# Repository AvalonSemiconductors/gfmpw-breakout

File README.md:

# gfmpw-breakout
This repo contains all the files, including production-ready gerber files, for this PCB:

It contains all components on-board to keep the caravel management controller happy and breaks out the user IO lines into the same footprint as a DIP-40 IC. The board is meant for both prototyping, i.e. on a breadboard, or use as a module on another PCB.

Specifically, it has:

 - Space for any GFMPW IC
 - Spiflash IC for mangement controller firmware, plus required level shifters and 3.3V voltage regulator
 - Programming header for SPI flash
 - Power-on reset circuitry
 - LED on ``gpio``
 - Breakouts for pins ``mprj_io[37:5]`` as well as ``mprj_io[0]``, ``mprj_io[1]`` and ``mprj_io[4]``

Note: the board does not have the capability to program the 25Q32 spiflash in-place. To program it, any number of portable ROM programmers can be used, such as the [CH341A](https://www.amazon.com/Programmer-Module-CH341A-Burner-5V-3-3V/dp/B07PFCJ8G9) (I recommend this device as it is supported by the `flashrom` utility on most Linux distros) and wire the programming header to it.

The pinout of the board is as such (a KiCad symbol is [also available](board_symbol.kicad_sym)):

Note that 3V3 is a output from the on-board voltage regulator. The only power input is 5V.

To edit the KiCad files, you will need to add the ``Caravel_Board.pretty`` footprint files from the efabless/caravel_board repo, which can be obtained [here](https://github.com/efabless/caravel_board/tree/main/hardware/footprints/Caravel_Board.pretty).

# BOM

| Designator(s) | Value       | TME # | Mouser # |
|---------------|-------------|-------|----------|
| U1         | AMS1117-3.3 | AZ1117H-3.3TRE1 | 595-REG1117-3.3 |
| U2         | 25Q32 or compatible       | MX25L1006EMI-10G | 454-W25Q32JVSSIMTR |
| U3         | MCP1319MT | MCP1319MT-29LT | 579-MCP1319MT29LE/OT |
| U4         | GFMPW IC | N/A | N/A |
| U5, U6, U7, U8 | SN74LV1T126 | - |  595-74LV1T126QDBVRQ1 |
| D1, D2 | LED 1206 (metric 3216) | 24-21SURC/S530-A2 | 630-HSMH-H150 |
| R4, R5, R6 | 1K 1206 (metric 3216) | 1206S4F1001T5E | 71-RCA12061K00JNEA |
| C1, C2, C3 | 1µF 0805 (metric 2012) | 08053C105J4T2A | 810-CGA4J3X7R1H105MS |

Assembled board should look like this:

After building, the programmer hookup (CH341A) is like follows. This may even work for in-system programming, but the programmer powers the board, so its intended to be a standalone setup.
Note that connecting the programmer holds caravel in reset until the physical connections to the programmer are disconnected.

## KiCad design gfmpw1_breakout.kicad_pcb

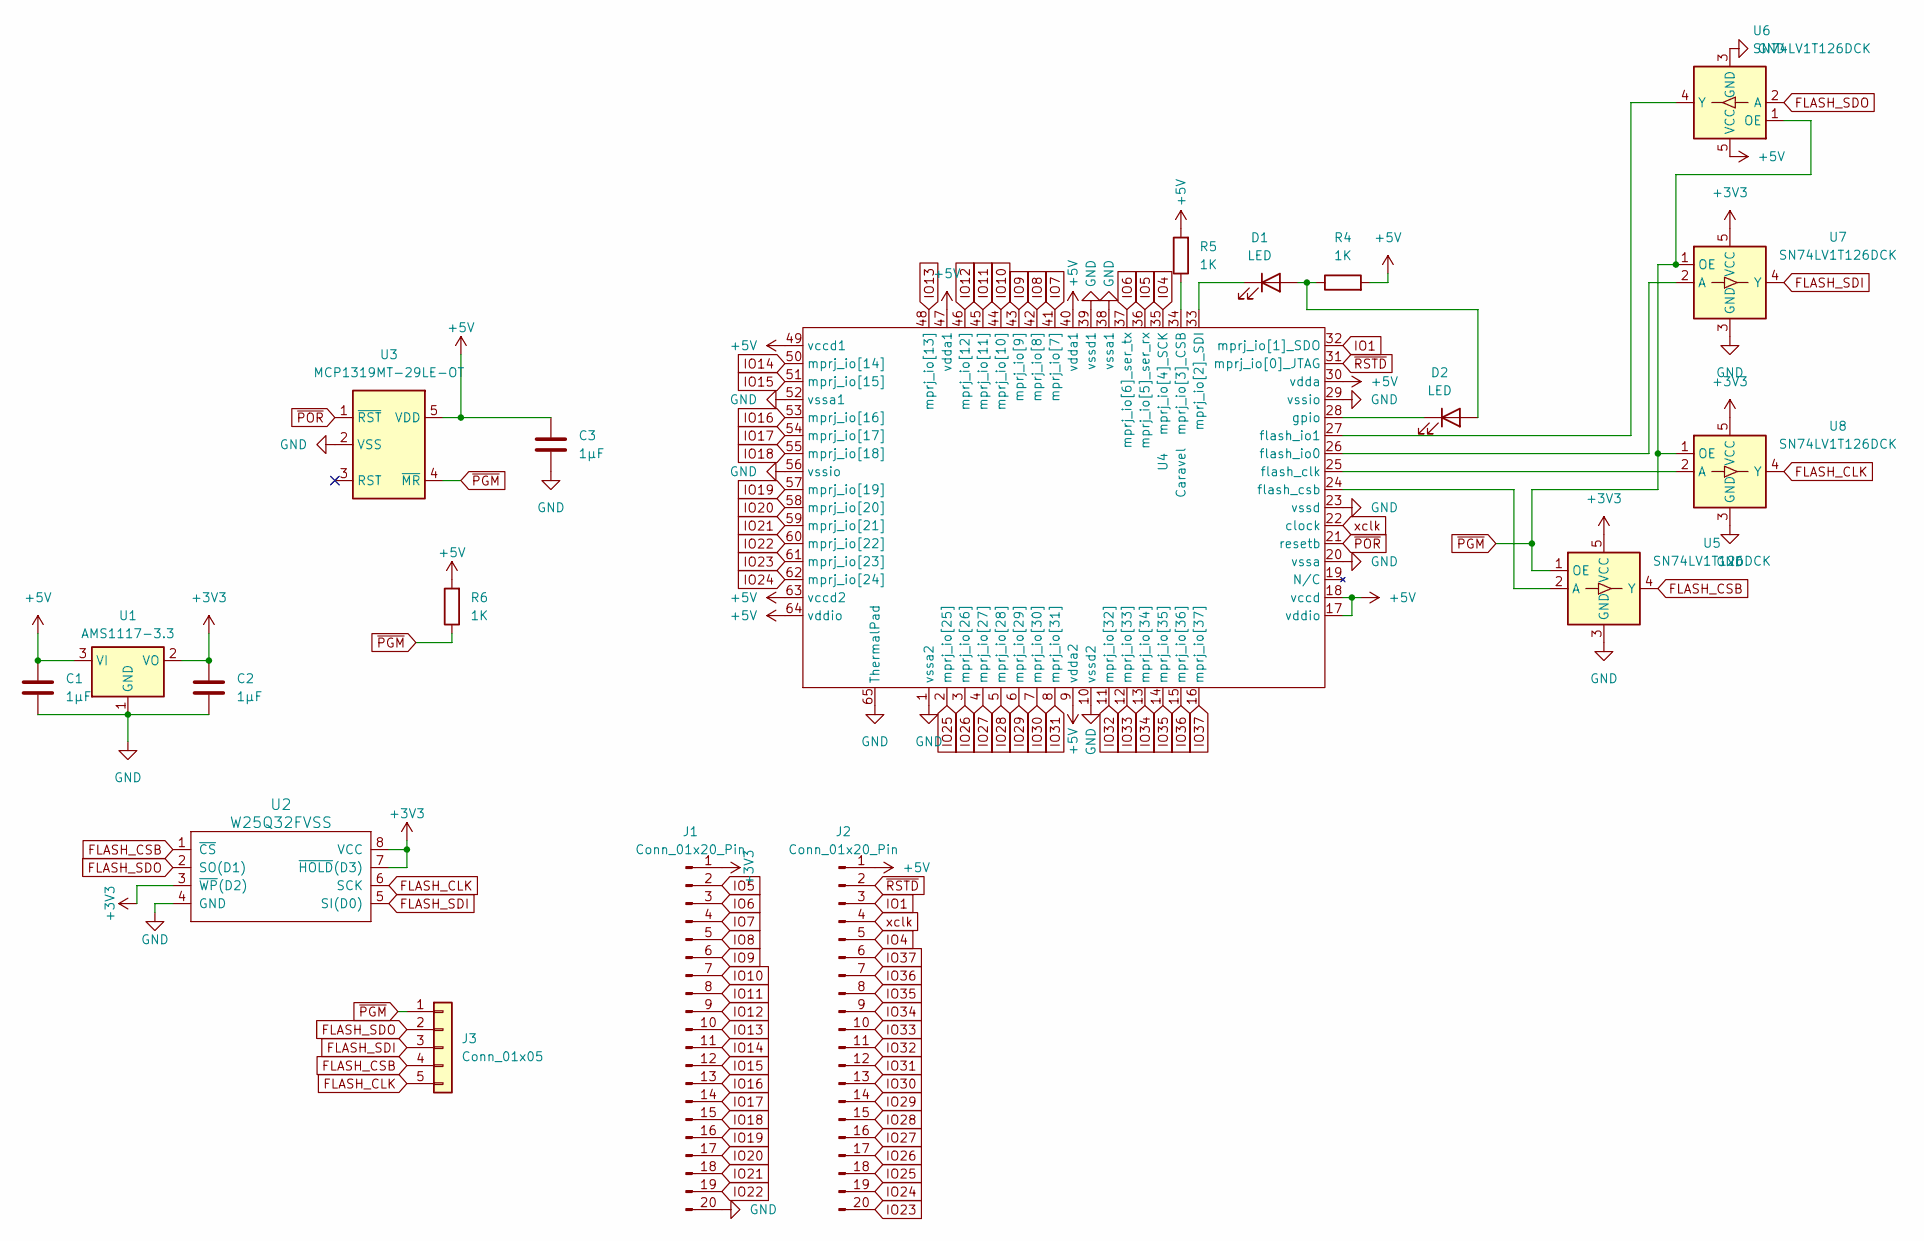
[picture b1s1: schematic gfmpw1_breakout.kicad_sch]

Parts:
C1, C2, C3: 1µF; C_0805_2012Metric_Pad1.18x1.45mm_HandSolder
D1, D2: LED; LED_1206_3216Metric_Pad1.42x1.75mm_HandSolder
J1, J2: Conn_01x20_Pin; PinHeader_1x20_P2.54mm_Vertical
J3: Conn_01x05; PinHeader_1x05_P2.54mm_Vertical
R4, R5, R6: 1K; R_1206_3216Metric_Pad1.30x1.75mm_HandSolder
U1: AMS1117-3.3; SOT-223-3_TabPin2
U2: W25Q32FVSS; SOIC-8_5.3x5.3mm_P1.27mm
U3: MCP1319MT-29LE-OT; PoR_5_SOT23
U4: Caravel; QFN-64-1EP_9x9mm_P0.5mm_EP7.65x7.65mm
U5, U6, U7, U8: SN74LV1T126DCK; SOT-23-5

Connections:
+3V3: C2.1, J1.1, U1.2 (VO), U2.3 (~WP(D2)), U2.7 (~HOLD(D3)), U2.8 (VCC), U5.5 (VCC), U7.5 (VCC), U8.5 (VCC)
+5V: C1.1, C3.2, J2.1, R4.2, R5.2, R6.2, U1.3 (VI), U3.5 (VDD), U4.9 (vdda2), U4.17 (vddio), U4.18 (vccd), U4.30 (vdda), U4.40 (vdda1), U4.47 (vdda1), U4.49 (vccd1), U4.63 (vccd2), U4.64 (vddio), U6.5 (VCC)
FLASH_CLK: J3.5, U2.6 (SCK), U8.4 (Y)
FLASH_CSB: J3.4, U2.1 (~CS), U5.4 (Y)
FLASH_SDI: J3.3, U2.5 (SI(D0)), U7.4 (Y)
FLASH_SDO: J3.2, U2.2 (SO(D1)), U6.2 (A)
GND: C1.2, C2.2, C3.1, J1.20, U1.1 (GND), U2.4 (GND), U3.2 (VSS), U4.1 (vssa2), U4.10 (vssd2), U4.20 (vssa), U4.23 (vssd), U4.29 (vssio), U4.38 (vssa1), U4.39 (vssd1), U4.52 (vssa1), U4.56 (vssio), U4.65 (ThermalPad), U5.3 (GND), U6.3 (GND), U7.3 (GND), U8.3 (GND)
IO1: J2.3, U4.32 (mprj_io[1]_SDO)
IO4: J2.5, U4.35 (mprj_io[4]_SCK)
IO5: J1.2, U4.36 (mprj_io[5]_ser_rx)
IO6: J1.3, U4.37 (mprj_io[6]_ser_tx)
IO7: J1.4, U4.41 (mprj_io[7])
IO8: J1.5, U4.42 (mprj_io[8])
IO9: J1.6, U4.43 (mprj_io[9])
IO10: J1.7, U4.44 (mprj_io[10])
IO11: J1.8, U4.45 (mprj_io[11])
IO12: J1.9, U4.46 (mprj_io[12])
IO13: J1.10, U4.48 (mprj_io[13])
IO14: J1.11, U4.50 (mprj_io[14])
IO15: J1.12, U4.51 (mprj_io[15])
IO16: J1.13, U4.53 (mprj_io[16])
IO17: J1.14, U4.54 (mprj_io[17])
IO18: J1.15, U4.55 (mprj_io[18])
IO19: J1.16, U4.57 (mprj_io[19])
IO20: J1.17, U4.58 (mprj_io[20])
IO21: J1.18, U4.59 (mprj_io[21])
IO22: J1.19, U4.60 (mprj_io[22])
IO23: J2.20, U4.61 (mprj_io[23])
IO24: J2.19, U4.62 (mprj_io[24])
IO25: J2.18, U4.2 (mprj_io[25])
IO26: J2.17, U4.3 (mprj_io[26])
IO27: J2.16, U4.4 (mprj_io[27])
IO28: J2.15, U4.5 (mprj_io[28])
IO29: J2.14, U4.6 (mprj_io[29])
IO30: J2.13, U4.7 (mprj_io[30])
IO31: J2.12, U4.8 (mprj_io[31])
IO32: J2.11, U4.11 (mprj_io[32])
IO33: J2.10, U4.12 (mprj_io[33])
IO34: J2.9, U4.13 (mprj_io[34])
IO35: J2.8, U4.14 (mprj_io[35])
IO36: J2.7, U4.15 (mprj_io[36])
IO37: J2.6, U4.16 (mprj_io[37])
unnamed: D1.2 (A), D2.2 (A), R4.1
unnamed: D1.1 (K), U4.33 (mprj_io[2]_SDI)
unnamed: D2.1 (K), U4.28 (gpio)
unnamed: U4.25 (flash_clk), U8.2 (A)
unnamed: U4.24 (flash_csb), U5.2 (A)
unnamed: U4.26 (flash_io0), U7.2 (A)
unnamed: U4.27 (flash_io1), U6.4 (Y)
unnamed: R5.1, U4.34 (mprj_io[3]_CSB)
xclk: J2.4, U4.22 (clock)
~PGM: J3.1, R6.1, U3.4 (~MR), U5.1 (OE), U6.1 (OE), U7.1 (OE), U8.1 (OE)
~POR: U3.1 (~RST), U4.21 (resetb)
~RSTD: J2.2, U4.31 (mprj_io[0]_JTAG)

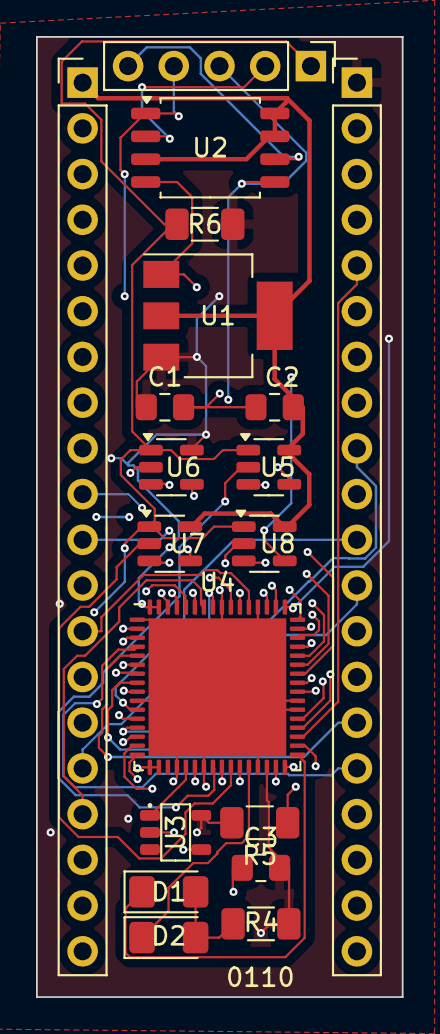
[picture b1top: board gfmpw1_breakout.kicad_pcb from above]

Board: 4 copper layers, 20.3 x 53.3 mm, 19 parts (0 on the bottom side), 54 nets.

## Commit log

2024-02-19 KiCad symbol file
2024-02-19 The rest of the files.
2025-03-23 Revision 2
2025-06-18 Documentation updates & minor PCB file fix.
